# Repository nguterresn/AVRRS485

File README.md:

# AVR RS485  

## Contents

- [System Concept](#System-Concept)
- [USART Configuration](#USART-Configuration)
- [Frame Format](#Frame-Format)
- [Transmission](#Transmission)
	- [Address Frame](#Address-Frame)
	- [Data Frame](#Data-Frame)
- [Reception](#Reception)
- [Setup](#Setup)
- [System Diagram](#System-Diagram)
	- [Multi-processor Communication Mode](#Multi-processor-Communication-Mode)
	- [LED Commands](#LED-Commands)
- [PCB](#PCB)
	- [Schematic](#Schematic)
	- [PCB Design](#PCB-Design)

### System Concept

### USART Configuration

### Initialization

Since the [PlatformIO](https://platformio.org) serial monitor is set to a baudrate of 9600, the USART baudrate should be 9600 in order to monitor data:

```
#define FOSC 16000000 
#define BAUD 9600
#define MYUBRR FOSC/16/BAUD-1
```
###### Note: Microcontroller frequency is set to 16 MHz.

To be able to use USART, the receiver (RX) and the transmitter (TX) should be enable:
```
UCSR0B = (1<<RXEN0)|(1<<TXEN0)|(1<<UCSZ02);
```

The frame format should have a **9th bit** to distinguish between address frames and data frames (+1 stop bits):
```
UCSR0C = (1<<UCSZ00)|(1<<UCSZ01);
```

### Frame Format

Frame | start | 0 | 1 | 2 | 3 | 4 | 5 | 6 | 7 | 8 | stopbit 
--- | --- | --- | --- |--- |--- |--- |--- |--- |--- |--- |--- 
Bit | LOW | X | X | X | X | X | X | X | X | X | HIGH 

### Transmission

#### Address Frame

To send an Address Frame:

```
send_addr(SLAVE1_ADDR);
```

Waits until the channel is empty, saves 1 into TXB8 (9 bit) and sends address:

```
...
while (!(UCSR0A & (1<<UDRE0)));

UCSR0B |= (1<<TXB80);

UDR0 = addr;
```

#### Data Frame

To send a Data Frame:

```
send_data(ON);
...
send_data(OFF);
```

Waits until the channel is empty, saves 0 into TXB8 (9 bit) and sends data:

```
...
while (!(UCSR0A & (1<<UDRE0)));

UCSR0B &= ~(1<<TXB80);

UDR0 = data;
```

### Reception

To receive, call:

```
get_data(&ADDRESS or &DATATYPE):
```

Waits for until receives something and checks if one of these error occur:

- Frame Error
- Data OverRun

```
...
while (!(UCSR0A & (1<<RXC0)));

if (UCSR0A & ((1<<FE0)|(1<<DOR0)))
	return ERROR;
```

###### Note: Frame Error happens when, i.e., the next character of stop bit is 0. 
###### Note: Data OverRun occurs when the receive buffer is full.
###### Note: USART Parity Error (UPE0) is not enable since there is no parity bit in the initialize frame.

After checking errors appearance, ninth bit is filtered from UCSR0B register and it is returned. The parameter buffer is updated with new received data from *UDR0*:

```
...
ninthbit = (ninthbit >> 1) & 0x01; 

*buffer = UDR0;

return ninthbit;
```

### Setup

LED and RS485 Enable Pin is setup as an Output. 

```
pinMode(LED_PIN, OUTPUT);
pinMode(WREN_PIN, OUTPUT);
```

To read the digital values of the DIP Switch, pull-up resistors are enable and node address is calculated:

```
pinMode(ADDR0_PIN, INPUT_PULLUP);
pinMode(ADDR1_PIN, INPUT_PULLUP);
pinMode(ADDR2_PIN, INPUT_PULLUP);
pinMode(ADDR3_PIN, INPUT_PULLUP);

ADDR = digitalRead(ADDR0_PIN) | digitalRead(ADDR1_PIN)<<1 | digitalRead(ADDR2_PIN)<<2 | digitalRead(ADDR3_PIN)<<3;
```

In case of master address, the pull-up resistors connected to the buttons are enable and the RS485 enable pin (WREN_PIN) is set to 1, in order to be able to send data to the slaves:

```
if (ADDR == MASTER_ADDR) {

	pinMode(BUT1_PIN, INPUT_PULLUP);
	pinMode(BUT2_PIN, INPUT_PULLUP);
	
	digitalWrite(WREN_PIN, HIGH);
	
} 
```

On the other hand, the Multi-processor Communication Mode is disable, the LED is turned off and the RS485 enable pin (WREN_PIN) is set to 0, in order to be able to receive data from the master:

```
/* SLAVE */
else
{
	/* Multi-processor Communication Mode */
	UCSR0A = (1<<MPCM0);
	
	digitalWrite(LED_PIN, LOW);
	
	digitalWrite(WREN_PIN, LOW);
}
```

### System Diagram
#### Master-Slave - Slave Side

#### Multi-processor Communication Mode

This method allows to distinguish between address and datatype frames. When a node is considered addressed, the multi-processor communication mode is enable, it only receives datatype commands and discards address frames, until multi-processor communication mode is disable:

```
...
/* If address received from master matches the local address set by the DIP switches. */

/* ADDRESSED */
if (ADDR_R == ADDR) {
	
	/* Multi-processor Communication Mode ENABLE */
	UCSR0A &= 0xfe; 
	
	/* Received frames are all of datatype format, addressed ones are discarded */
	
	/* Multi-processor Communication Mode DISABLE */
	UCSR0A |= (1<<MPCM0); 

} 
```

#### LED Commands

The LED is turned on and turned off by received ON and OFF (from the master), respectively, with value 255 and 127.
This received value is shifted 7 bits to have a value between 0 and 1, in order to command the LED:

```
...
digitalWrite(LED_PIN, data>>7 & 0x01);
...
```

### PCB
This circuit was designed to be easily tested and programmed. In addition to the mandatory requirements, a FT232 interface, a AVR ISP and a 5V voltage regulator was added as optional requirements. 
- The FT232 interface will allow testing Rx and Tx communications using a [FTDI](https://en.wikipedia.org/wiki/FTDI) chip connected to a USB port, using a computer to track results. 
- The [ISP](https://www.elementzonline.com/image/cache/catalog/data/products/Programmers%20and%20Debuggers/USBasp/isp_header-500x500.jpg) interface will allow uC to be programmed.
- 5V Voltage regulator (7805) allows acceptance of higher input voltages (up to 12V) without compromising the system behavior. 

#### Schematic

#### PCB Design

 - Trace's width: 0.3mm. Able to handle 1A through the circuit.

##### V0.1.1

##### V0.1.2
- Crystal Capacitors (22pF) were changed to ceramic to match crystal performance requirements.

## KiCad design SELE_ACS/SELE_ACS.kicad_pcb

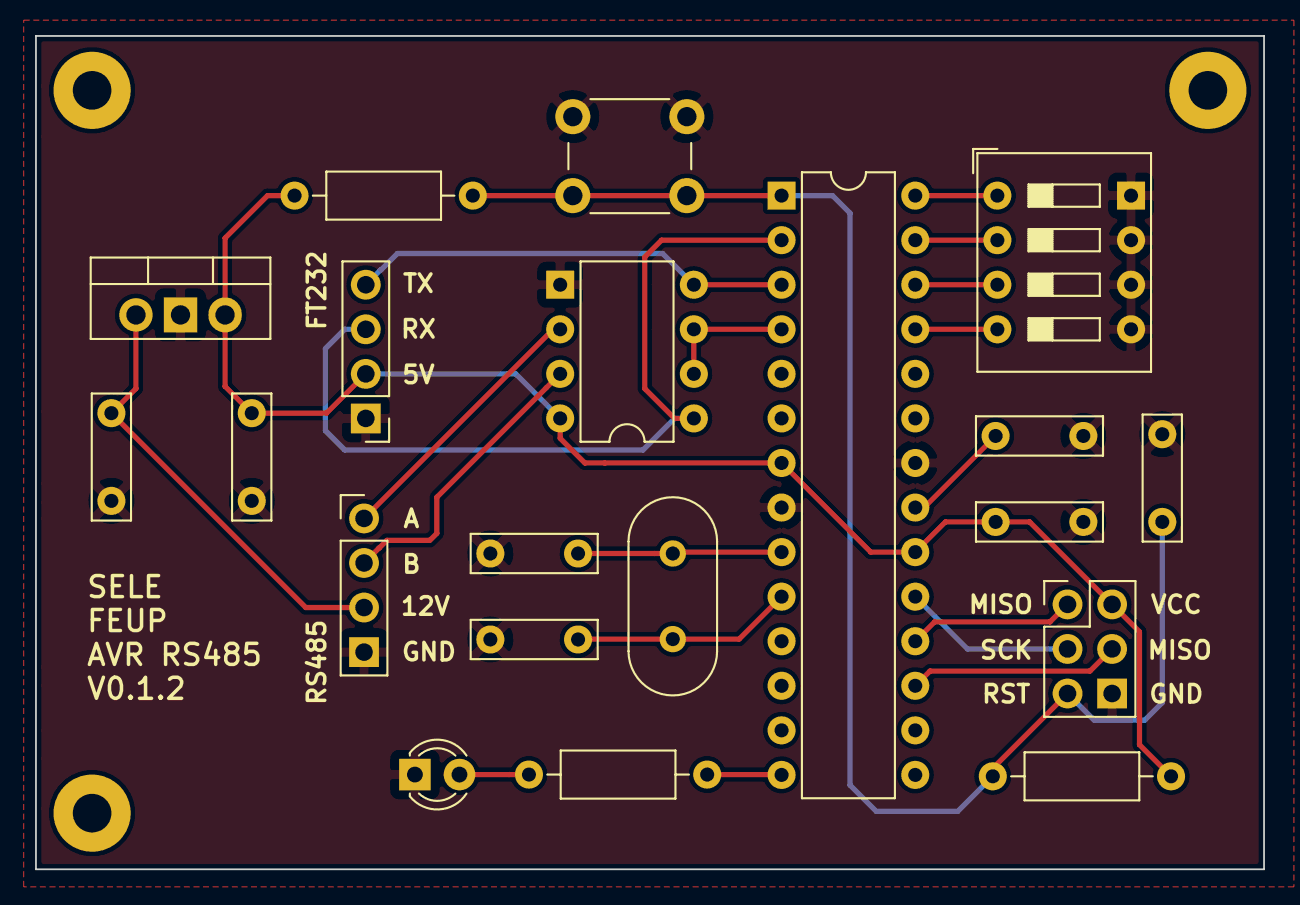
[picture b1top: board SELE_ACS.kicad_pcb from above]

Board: 2 copper layers, 70.0 x 47.5 mm, 20 parts (0 on the bottom side), 21 nets.

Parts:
C1, C2: 22pF; C_Rect_L7.0mm_W2.0mm_P5.00mm
C3, C4: 100nF; C_Rect_L7.0mm_W2.0mm_P5.00mm
C5: 10nF; C_Rect_L7.0mm_W2.0mm_P5.00mm
C6: 0.33uF; C_Rect_L7.0mm_W2.0mm_P5.00mm
C7: 0.1uF; C_Rect_L7.0mm_W2.0mm_P5.00mm
D1: LED; LED_D3.0mm
J1: AVR-ISP-6; PinHeader_2x03_P2.54mm_Vertical
J2: Input Cables; PinHeader_1x04_P2.54mm_Vertical
J3: FT232 Adapter; Socket_Strip_Straight_1x04_Pitch2.54mm
R1: 330; R_Axial_DIN0207_L6.3mm_D2.5mm_P10.16mm_Horizontal
R2: 4.7k; R_Axial_DIN0207_L6.3mm_D2.5mm_P10.16mm_Horizontal
R3: 47k; R_Axial_DIN0207_L6.3mm_D2.5mm_P10.16mm_Horizontal
SW1: Button Reset; SW_PUSH_6mm
SW2: SW_DIP_x04; SW_DIP_SPSTx04_Slide_9.78x12.34mm_W7.62mm_P2.54mm
U1: atmega328p; DIP-28_W7.62mm
U2: MAX485E; DIP-8_W7.62mm
U3: LM7805_TO220; TO-220-3_Vertical
Y1: Crystal 8MHz; Crystal_HC49-U_Vertical

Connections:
+12V: C6.1, J2.3, U3.1
A: J2.1, U2.6
AREF: C3.1, U1.21
AVCC: C4.1, C7.1, J1.2, J3.2, R2.1, R3.2, U1.7, U1.20, U2.8, U3.3
B: J2.2, U2.7
ENABLE: U1.4, U2.2, U2.3
GND: C1.2, C2.2, C3.2, C4.2, C5.1, C6.2, C7.2, D1.1, J1.6, J2.4, J3.1, SW1.2, SW2.5, SW2.6, SW2.7, SW2.8, U1.8, U1.22, U2.5, U3.2
LED: R1.2, U1.14
MISO: J1.1, U1.18
MOSI: J1.4, U1.17
unnamed: D1.2, R1.1
PC2: SW2.4, U1.25
PC3: SW2.3, U1.26
PC4: SW2.2, U1.27
PC5: SW2.1, U1.28
RESET: C5.2, J1.5, R2.2, R3.1, SW1.1, U1.1
RX: J3.3, U1.2, U2.1
SCK: J1.3, U1.19
TX: J3.4, U1.3, U2.4
XTAL1: C1.1, U1.9, Y1.1
XTAL2: C2.1, U1.10, Y1.2

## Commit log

2019-11-13 Sch done
2019-11-14 Add files via upload
    7805 e ft232 adapter
2019-11-16 Add files via upload
    pcbnew added
    socket symbol, footprint and 3d model added
2019-11-17 Add files via upload
    new pub
2019-11-17 Add files via upload
    gerber up
2019-11-20 Add files via upload
    v0.1.2
2019-11-20 fgsdfg
2019-11-20 PIO added
2019-11-25 Update README.md
    wiki improvements
2019-11-25 Update README.md
    minor improvs
2019-11-25 Update README.md
    add shields
2019-11-29 deleted double stop bit
2019-11-29 DFVSDF
2019-11-29 working
2019-12-02 add contents
2019-12-02 Update README.md
    add contents
2019-12-04 add 9 bit
